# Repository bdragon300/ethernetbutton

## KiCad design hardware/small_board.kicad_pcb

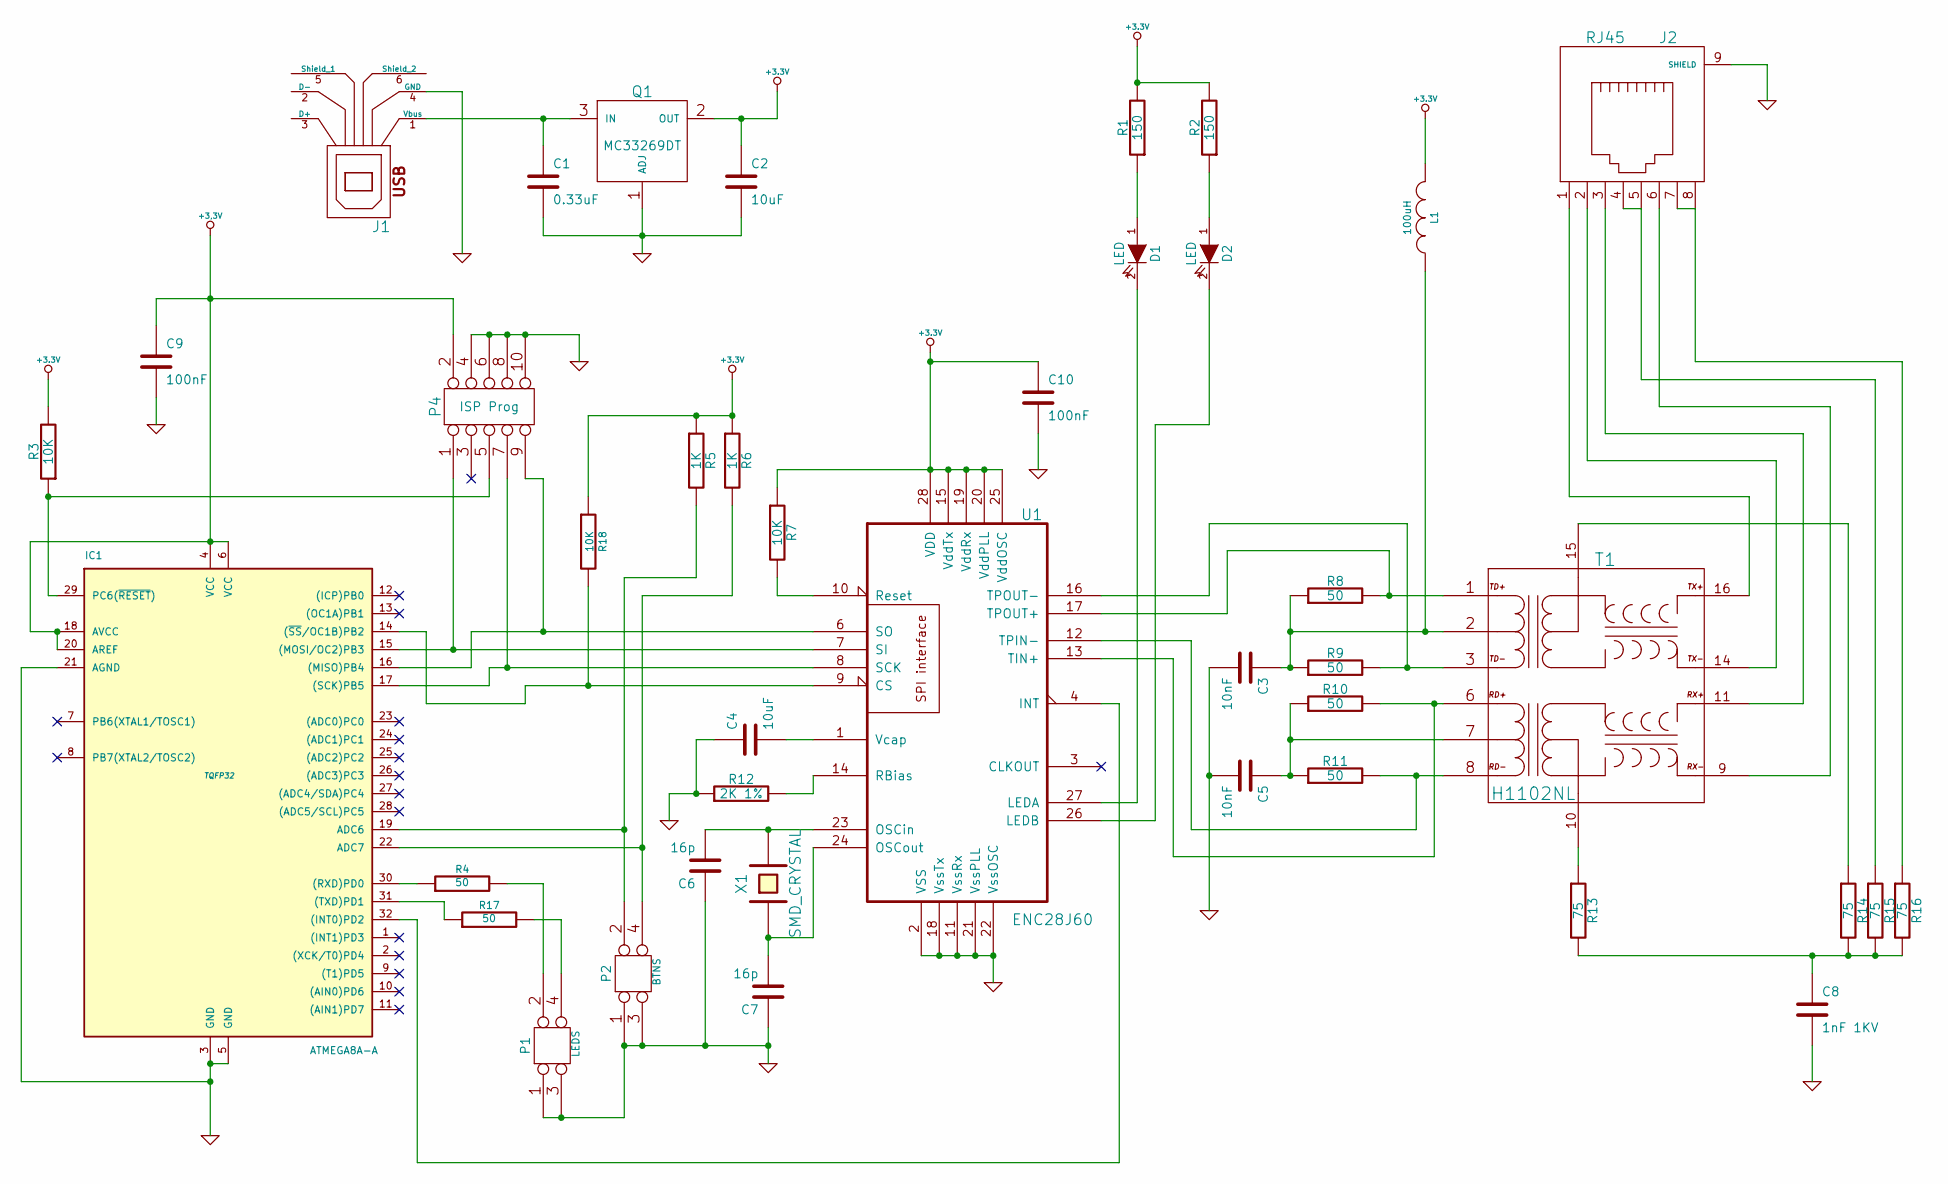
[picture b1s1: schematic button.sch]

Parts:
C1: 0.33uF
C2, C4: 10uF
C3, C5: 10nF
C6, C7: 16p
C8: 1nF 1KV
C9, C10: 100nF
D1, D2: LED
IC1: ATMEGA8A-A; TQFP32
J1: USB_1
J2: RJ45
L1: 100uH
P1: LEDS
P2: BTNS
P4: ISP Prog
Q1: MC33269DT
R1, R2: 150
R3, R7: 10K
R4, R17: 50
R5, R6: 1K
R8, R9, R10, R11: 50
R12: 2K 1%
R13, R14, R15, R16: 75
R18: 10K
T1: H1102NL
U1: ENC28J60
X1: SMD_CRYSTAL

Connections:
GND: C1.2, C2.2, C3.2, C4.1, C5.2, C6.1, C7.1, C8.2, C9.2, C10.2, IC1.3 (GND), IC1.5 (GND), IC1.21 (AGND), J1.4 (GND), J2.9 (SHIELD), P1.1, P1.3, P2.1, P2.3, P4.4, P4.6, P4.8, P4.10, Q1.1 (ADJ), R12.1, U1.2 (VSS), U1.11 (VssRx), U1.18 (VssTx), U1.21 (VssPLL), U1.22 (VssOSC)
unnamed: R12.2, U1.14 (RBias)
unnamed: C1.1, J1.1 (Vbus), Q1.3 (IN)
unnamed: D1.2 (K), U1.27 (LEDA)
unnamed: C7.2, U1.24 (OSCout), X1.1
unnamed: R14.1, T1.15
unnamed: C3.1, L1.1, R8.1, R9.1, T1.2 (PM)
unnamed: R10.2, T1.6 (PR1), U1.13 (TIN+)
unnamed: R7.2, U1.10 (Reset)
unnamed: C4.2, U1.1 (Vcap)
unnamed: R9.2, T1.3 (PR2), U1.16 (TPOUT-)
unnamed: R8.2, T1.1 (PR1), U1.17 (TPOUT+)
unnamed: C5.1, R10.1, R11.1, T1.7 (PM)
unnamed: R13.1, T1.10
unnamed: P1.2, R4.2
unnamed: P1.4, R17.2
unnamed: IC1.17 ((SCK)PB5), P4.7, U1.8 (SCK)
unnamed: IC1.15 ((MOSI/OC2)PB3), P4.1, U1.7 (SI)
unnamed: J2.6, T1.9 (RX-)
unnamed: D2.1 (A), R2.1
unnamed: D1.1 (A), R1.1
unnamed: D2.2 (K), U1.26 (LEDB)
unnamed: J2.7, J2.8, R16.1
unnamed: J2.4, J2.5, R15.1
unnamed: J2.3, T1.11 (RX+)
unnamed: J2.2, T1.14 (TX-)
unnamed: J2.1, T1.16 (TX+)
unnamed: IC1.22 (ADC7), P2.4, R6.2
unnamed: IC1.31 ((TXD)PD1), R17.1
unnamed: IC1.30 ((RXD)PD0), R4.1
unnamed: IC1.19 (ADC6), P2.2, R5.2
unnamed: IC1.14 ((~SS~/OC1B)PB2), R18.2, U1.9 (CS)
unnamed: IC1.16 ((MISO)PB4), P4.9, U1.6 (SO)
unnamed: C8.1, R13.2, R14.2, R15.2, R16.2
unnamed: R11.2, T1.8 (PR2), U1.12 (TPIN-)
unnamed: IC1.29 (PC6(~RESET~)), P4.5, R3.1
unnamed: C6.2, U1.23 (OSCin), X1.3
unnamed: IC1.32 ((INT0)PD2), U1.4 (INT)

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
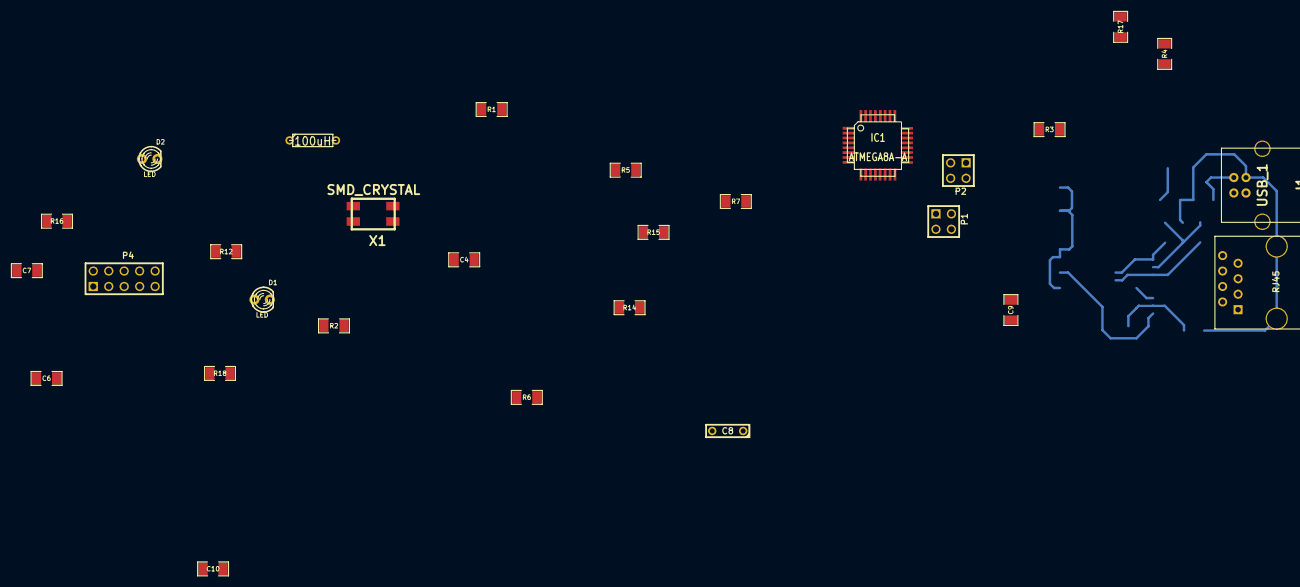
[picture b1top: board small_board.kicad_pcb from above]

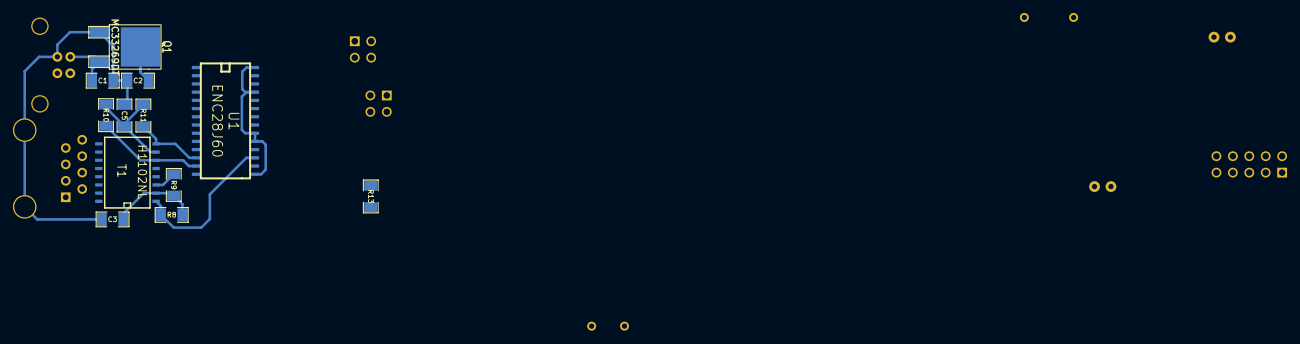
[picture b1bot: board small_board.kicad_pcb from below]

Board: 2 copper layers, 41 parts (12 on the bottom side), 39 nets.

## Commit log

2020-12-09 Initial commit, put old code to git
